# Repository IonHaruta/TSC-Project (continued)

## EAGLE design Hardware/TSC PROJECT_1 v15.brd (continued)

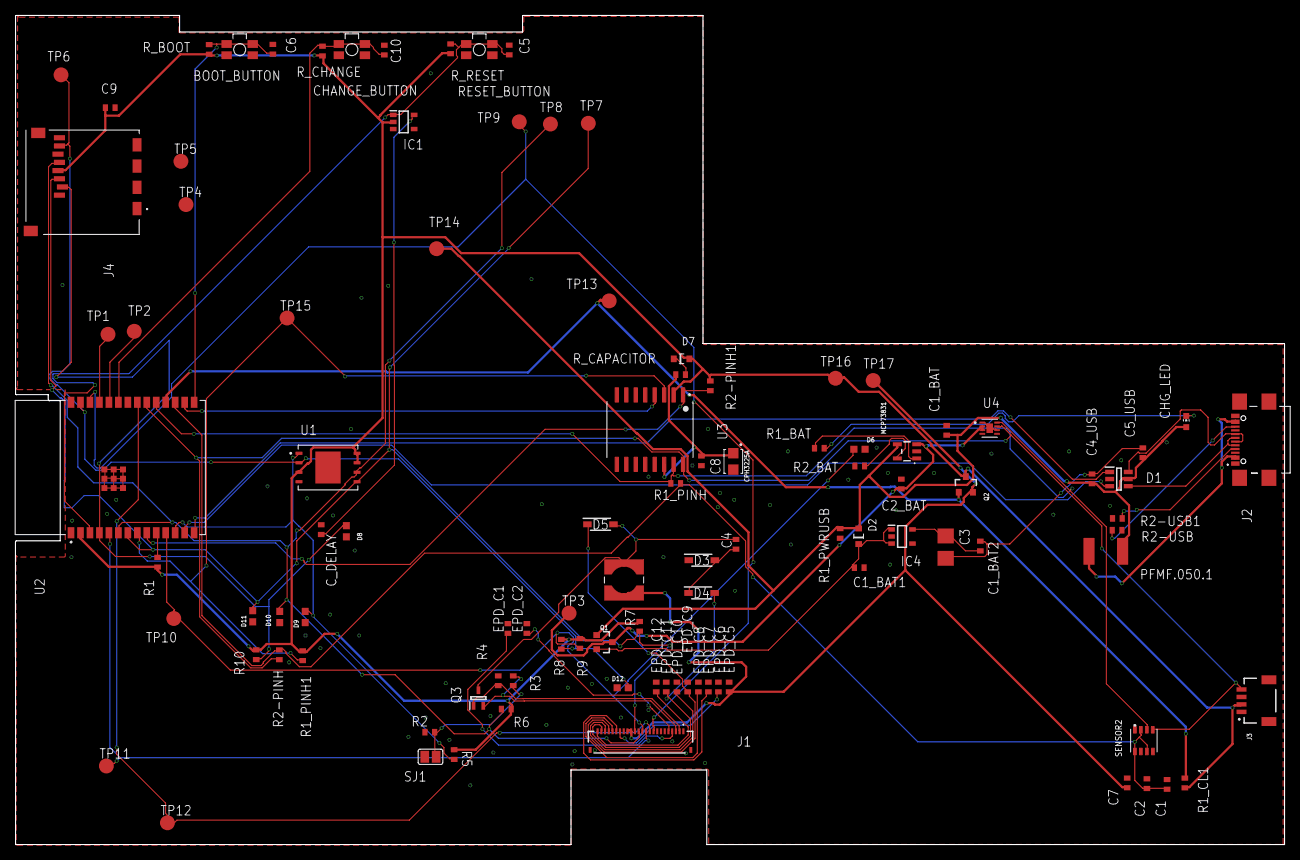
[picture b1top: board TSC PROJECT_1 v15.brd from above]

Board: 2 copper layers, 170.2 x 111.2 mm, 103 parts (0 on the bottom side), 57 nets.

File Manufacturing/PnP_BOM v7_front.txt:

BOOT_BUTTON	33.87	118.28	180.00	BUTTON_CUSYOMV1	MYBUTTON
C1	158.26	19.73	90.00		EAGLE-LTSPICE_C0402
C10	53.27	118.22	90.00		EAGLE-LTSPICE_C0402
C1_BAT	128.70	67.22	90.00		EAGLE-LTSPICE_C0402
C1_BAT1	116.97	48.80	0.00		EAGLE-LTSPICE_C0402
C1_BAT2	133.21	51.70	90.00		EAGLE-LTSPICE_C0402
C2	155.55	19.83	90.00		EAGLE-LTSPICE_C0402
C2_BAT	122.61	60.02	90.00		EAGLE-LTSPICE_C0402
C3	128.56	51.55	270.00		RCL_CT3528
C4	100.44	51.93	90.00		EAGLE-LTSPICE_C0402
C4_USB	148.20	60.71	90.00		EAGLE-LTSPICE_C0402
C5	70.03	118.23	90.00		EAGLE-LTSPICE_C0402
C5_USB	155.01	64.21	90.00		EAGLE-LTSPICE_C0402
C6	38.32	118.33	90.00		EAGLE-LTSPICE_C0402
C7	152.91	19.93	90.00		EAGLE-LTSPICE_C0402
C8	95.80	63.13	270.00		EAGLE-LTSPICE_C0402
C9	16.51	110.49	0.00		EAGLE-LTSPICE_C0402
CHANGE_BUTTON	48.92	118.28	180.00	BUTTON_CUSYOMV1	MYBUTTON
CHG_LED	160.83	68.40	0.00		ADAFRUIT_CHIP-LED0603
CPH3225A	100.08	63.05	270.00	CPH3225A	CAPCP3225X100N
C_DELAY	44.81	53.90	90.00		EAGLE-LTSPICE_C0402
D1	151.80	60.68	0.00	USBLC6-2SC6Y	SOT95P280X145-6N
D10	39.24	42.18	90.00	PGB1010603MR	DIOC1608X36N
D11	35.62	42.28	90.00	PGB1010603MR	DIOC1608X36N
D12	85.25	32.69	0.00	PGB1010603MR	DIOC1608X36N
D2	116.89	53.01	90.00	ESP32_WROVER_AVX---SD0805S020S1R0_AVX_SD0805S020S1R0_0_0AVX_SD0805S020S1R0_0_0	ESP32_WROVER_AVX---SD0805S020S1R0_AVX_SD0805S020S1R0_0
D3	95.85	49.80	0.00	MBR0530	SOD3716X135N
D4	95.82	45.41	0.00	MBR0530	SOD3716X135N
D5	82.26	54.61	0.00	MBR0530	SOD3716X135N
D6	117.00	64.68	180.00	PGB1010603MR	DIOC1608X36N
D7	93.14	76.81	0.00	ESP32_WROVER_AVX---SD0805S020S1R0_AVX_SD0805S020S1R0_0_0AVX_SD0805S020S1R0_0_0	ESP32_WROVER_AVX---SD0805S020S1R0_AVX_SD0805S020S1R0_0
D8	48.18	53.68	90.00	PGB1010603MR	DIOC1608X36N
D9	42.66	42.18	90.00	PGB1010603MR	DIOC1608X36N
EPD_C1	69.85	40.64	90.00		EAGLE-LTSPICE_C0402
EPD_C10	92.52	32.79	90.00		EAGLE-LTSPICE_C0402
EPD_C11	91.08	32.79	90.00		EAGLE-LTSPICE_C0402
EPD_C12	89.74	32.79	90.00		EAGLE-LTSPICE_C0402
EPD_C2	72.39	40.64	90.00		EAGLE-LTSPICE_C0402
EPD_C5	99.52	32.79	90.00		EAGLE-LTSPICE_C0402
EPD_C6	98.08	32.79	90.00		EAGLE-LTSPICE_C0402
EPD_C7	96.74	32.79	90.00		EAGLE-LTSPICE_C0402
EPD_C8	95.40	32.79	90.00		EAGLE-LTSPICE_C0402
EPD_C9	93.96	32.79	90.00		EAGLE-LTSPICE_C0402
IC1	55.87	108.58	0.00	BD5229G-TR	SOT95P280X125-5N
IC4	122.71	52.98	0.00	XC6220A331MR-G	SOT95P280X120-5N
J1	87.63	25.60	0.00	FH34SRJ-24S-0.5SH_99_	FH34SRJ24S05SH99
J2	169.67	65.96	90.00	SAMACSYS_PARTS_USB4110-GF-A	SAMACSYS_PARTS_USB4110GFA
J3	170.08	30.96	90.00	QWIIC_RIGHT_ANGLE	JST04_1MM_RA
J4	12.98	100.54	270.00	112A-TAAR-R03_ATTEND	112ATAARR03ATTEND
L1	85.43	47.15	270.00	744043680IND_4828-WE-TPC_WRE	IND_4828-WE-TPC_WRE
MCP73831	123.38	64.40	90.00	ESP32_WROVER_SPARKFUN-IC-POWER_MCP73831	ESP32_WROVER_SPARKFUN-IC-POWER_SOT23-5
PFMF.050.1	150.04	50.99	0.00	ESP32C6_VARISTORCN1812	ESP32C6_VARISTOR_CT/CN1812
Q1	82.80	38.81	270.00	20V/4.2A/52mΩ/1.4W	ESP32_WROVER_SPARKFUN-DISCRETESEMI_SOT23-3
Q2	131.27	59.96	0.00	20V/4.2A/52mΩ/1.4W	ESP32_WROVER_SPARKFUN-DISCRETESEMI_SOT23-3
Q3	65.89	31.31	90.00	SI1308EDL-T1-GE3	SOT65P210X110-3N
R1	22.86	49.53	90.00		ESP32_WROVER_EAGLE-LTSPICE_R0402
R10	36.09	37.12	90.00		ESP32_WROVER_EAGLE-LTSPICE_R0402
R1_BAT	111.62	64.82	0.00		ESP32_WROVER_EAGLE-LTSPICE_R0402
R1_CL1	160.64	19.92	90.00		ESP32_WROVER_EAGLE-LTSPICE_R0402
R1_PINH	92.35	60.10	0.00		ESP32_WROVER_EAGLE-LTSPICE_R0402
R1_PINH1	42.32	36.99	90.00		ESP32_WROVER_EAGLE-LTSPICE_R0402
R1_PWRUSB	114.41	53.39	90.00		ESP32_WROVER_EAGLE-LTSPICE_R0402
R2	59.37	26.73	0.00		ESP32_WROVER_EAGLE-LTSPICE_R0402
R2-PINH	39.19	37.11	90.00		ESP32_WROVER_EAGLE-LTSPICE_R0402
R2-PINH1	97.00	73.19	90.00		ESP32_WROVER_EAGLE-LTSPICE_R0402
R2-USB	151.55	53.82	0.00		ESP32_WROVER_EAGLE-LTSPICE_R0402
R2-USB1	151.59	55.40	0.00		ESP32_WROVER_EAGLE-LTSPICE_R0402
R2_BAT	117.03	62.42	0.00		ESP32_WROVER_EAGLE-LTSPICE_R0402
R3	70.56	33.63	270.00		ESP32_WROVER_EAGLE-LTSPICE_R0402
R4	68.55	33.63	90.00		ESP32_WROVER_EAGLE-LTSPICE_R0402
R5	62.64	23.73	90.70		ESP32_WROVER_EAGLE-LTSPICE_R0402
R6	69.63	29.83	0.00		ESP32_WROVER_EAGLE-LTSPICE_R0402
R7	87.52	40.93	90.00		ESP32_WROVER_EAGLE-LTSPICE_R0402
R8	77.01	38.53	90.00		ESP32_WROVER_EAGLE-LTSPICE_R0402
R9	79.50	38.63	90.00		ESP32_WROVER_EAGLE-LTSPICE_R0402
RESET_BUTTON	66.01	118.28	180.00	BUTTON_CUSYOMV1	MYBUTTON
R_BOOT	29.78	118.31	90.00		ESP32_WROVER_EAGLE-LTSPICE_R0402
R_CAPACITOR	93.01	74.69	0.00		ESP32_WROVER_EAGLE-LTSPICE_R0402
R_CHANGE	44.98	118.09	90.00		ESP32_WROVER_EAGLE-LTSPICE_R0402
R_RESET	62.16	118.39	90.00		ESP32_WROVER_EAGLE-LTSPICE_R0402
SENSOR2	155.15	25.60	90.00	ESP32_WROVER_BME680_BME680	ESP32_WROVER_BME680_PSON80P300X300X100-8N
SJ1	59.46	23.43	0.00		SJ
TP1	16.21	80.10	0.00	TPTP20R	TP20R
TP10	25.03	41.98	0.00	TPTP20R	TP20R
TP11	15.99	22.20	0.00	TPTP20R	TP20R
TP12	24.18	14.58	0.00	TPTP20R	TP20R
TP13	83.43	84.58	0.00	TPTP20R	TP20R
TP14	60.28	91.58	0.00	TPTP20R	TP20R
TP15	40.23	82.28	0.00	TPTP20R	TP20R
TP16	113.79	74.20	0.00	TPTP20R	TP20R
TP17	118.84	73.90	0.00	TPTP20R	TP20R
TP2	19.73	80.50	0.00	TPTP20R	TP20R
TP3	78.05	42.70	0.00	TPTP20R	TP20R
TP4	26.67	97.50	0.00	TPTP20R	TP20R
TP5	25.99	103.30	0.00	TPTP20R	TP20R
TP6	9.91	114.90	0.00	TPTP20R	TP20R
TP7	80.63	108.40	0.00	TPTP20R	TP20R
TP8	75.55	108.30	0.00	TPTP20R	TP20R
TP9	71.37	108.60	0.00	TPTP20R	TP20R
U1	45.72	62.23	0.00	W25Q512JVEIQ	SON127P600X800X80-9N
U2	19.51	62.23	90.00	ESP32-C6-WROOM-1-N8	XCVR_ESP32-C6-WROOM-1-N8
U3	88.90	67.31	270.00	DS3231SN#	SOIC127P1032X265-16N
U4	134.47	67.50	0.00	MAX17048G+T10	SON50P200X200X80-9N

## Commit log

2025-04-07 TSC Project
2025-04-07 Create LICENSE
